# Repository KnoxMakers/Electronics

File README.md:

# Electronics
schematics, board files, firmware, slide decks, and the like

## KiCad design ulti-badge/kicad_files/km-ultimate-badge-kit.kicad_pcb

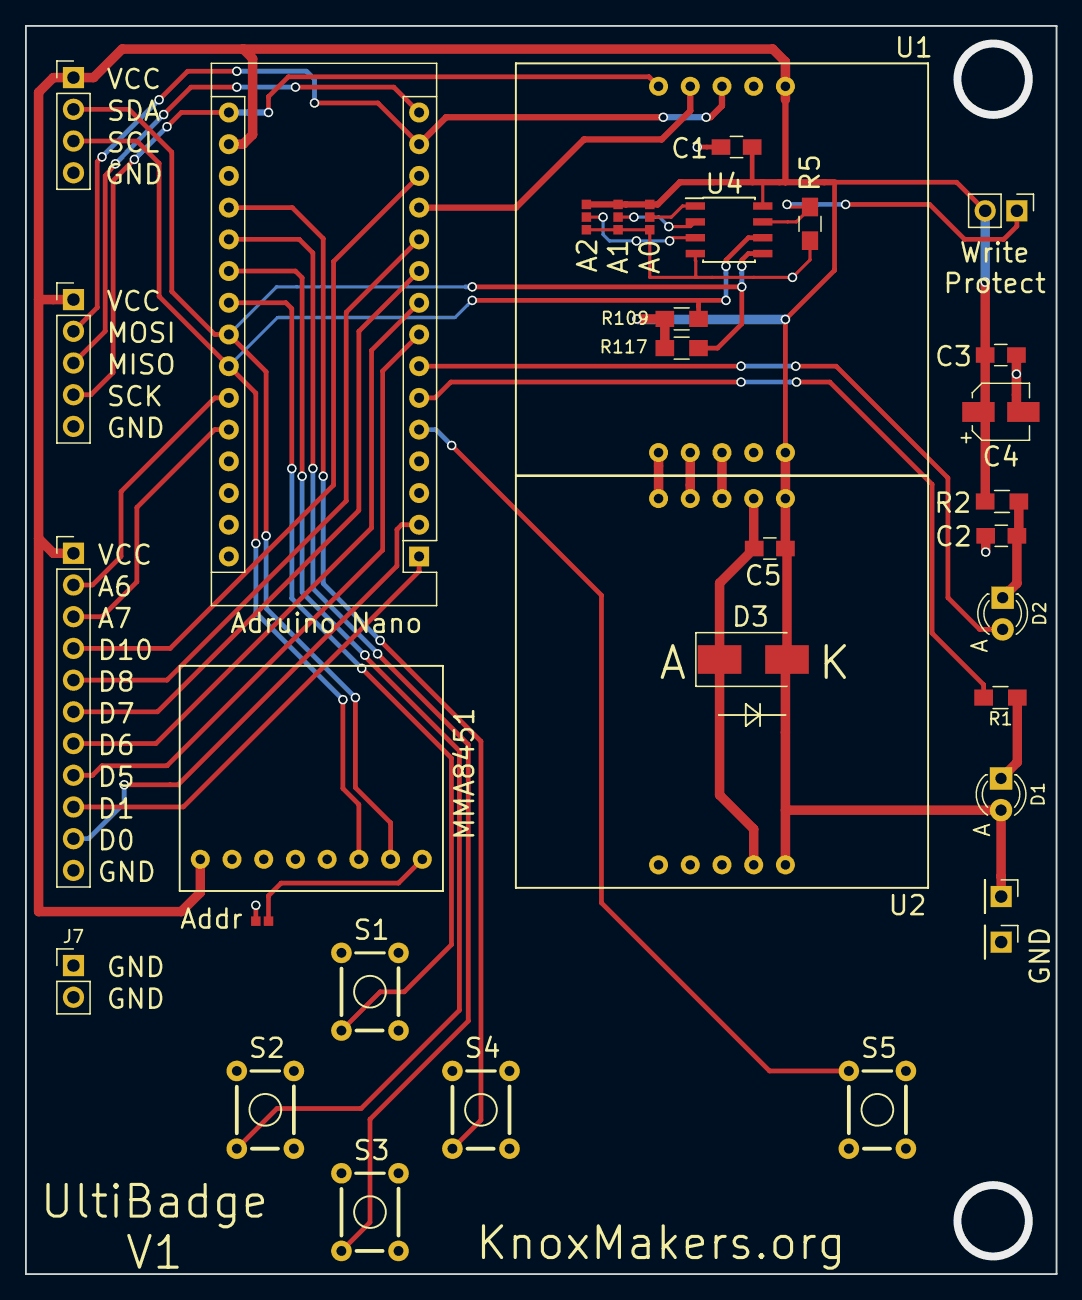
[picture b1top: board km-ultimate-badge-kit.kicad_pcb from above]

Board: 2 copper layers, 82.6 x 100.0 mm, 34 parts (0 on the bottom side), 34 nets.

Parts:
A1: Arduino_Nano_v3.x; Arduino_Nano
C1, C2, C5: 100n; C_0805_HandSoldering
C3: 0.1u; C_0805_HandSoldering
C4: 10u; CP_Elec_4x4.5
D1: LED; LED_D3.0mm
D2: D_Photo; LED_D3.0mm
D3: Diode; D_SMB_Handsoldering
J1: Conn_01x02_Male; Pin_Header_Straight_1x02_Pitch2.54mm
J2: Conn_01x11_Male; Pin_Header_Straight_1x11_Pitch2.54mm
J3, J4: Conn_01x01; Pin_Header_Straight_1x01_Pitch2.54mm
J5: Conn_01x04_Male; Pin_Header_Straight_1x04_Pitch2.54mm
J6: Conn_01x05_Male; Pin_Header_Straight_1x05_Pitch2.54mm
J7: Conn_01x02; Pin_Header_Straight_1x02_Pitch2.54mm
JP1, JP2, JP3: SolderJumper_3_Bridged12; SolderJumper_3_Pad
JP4: SolderJumper_2_Open; SolderJumper_2_Pad
R1: 20; R_0805_HandSoldering
R2: 100; R_0805_HandSoldering
R5: 10k; R_0805_HandSoldering
R109, R117: 4.7k; R_0805_HandSoldering
S1, S2, S3, S4, S5: Momentary_Push_Buttom_KM_6x6; Momentary_Push_Button_KM_6x6
U1, U2: 8x8_LED_Matrix; 8x8LED_Matrix
U3: MMA8451
U4: 24LC04; SOIC-8_3.9x4.9mm_Pitch1.27mm

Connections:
A6: A1.25, J2.2
A7: A1.26, J2.3
D0: A1.2, J2.10
D1: A1.1, J2.9
D5: A1.8, J2.8
D6: A1.9, J2.7
D7: A1.10, J2.6
D8: A1.11, J2.5
D10: A1.13, J2.4
DISPLAY_CS: A1.12, U1.4
GND: A1.4, A1.29, C1.2, C2.2, C3.2, C4.2, C5.2, D3.1, J2.11, J4.1, J5.4, J6.5, J7.1, J7.2, JP1.1, JP2.1, JP3.1, JP4.2, R5.1, S1.4, S2.4, S3.4, S4.4, S5.3, U1.2, U1.9, U2.2, U2.9, U3.2, U4.4
INT0: A1.5, S5.1
MISO: A1.15, J6.3
MOSI: A1.14, J6.2, U1.3
unnamed: C2.1, D2.1, R2.2
unnamed: D1.1, R1.1
unnamed: J1.1, R5.2, U4.7
unnamed: JP1.2, U4.3
unnamed: JP2.2, U4.2
unnamed: JP3.2, U4.1
unnamed: JP4.1, U3.8
unnamed: U1.6, U2.5
unnamed: U1.7, U2.4
unnamed: U1.8, U2.3
PB0: A1.19, S4.2
PB1: A1.20, S3.2
PB2: A1.21, S2.2
PB3: A1.22, S1.2
RX_DIODE: A1.7, D2.2
SCK: A1.16, J6.4, U1.5
SCL: A1.24, J5.3, R109.1, U3.6, U4.6
SDA: A1.23, J5.2, R117.1, U3.7, U4.5
TX_DIODE: A1.6, R1.2
VCC: A1.17, C1.1, C3.1, C4.1, C5.1, D1.2, D3.2, J1.2, J2.1, J3.1, J5.1, J6.1, JP1.3, JP2.3, JP3.3, R2.1, R109.2, R117.2, U1.1, U1.10, U2.1, U2.10, U3.1, U4.8

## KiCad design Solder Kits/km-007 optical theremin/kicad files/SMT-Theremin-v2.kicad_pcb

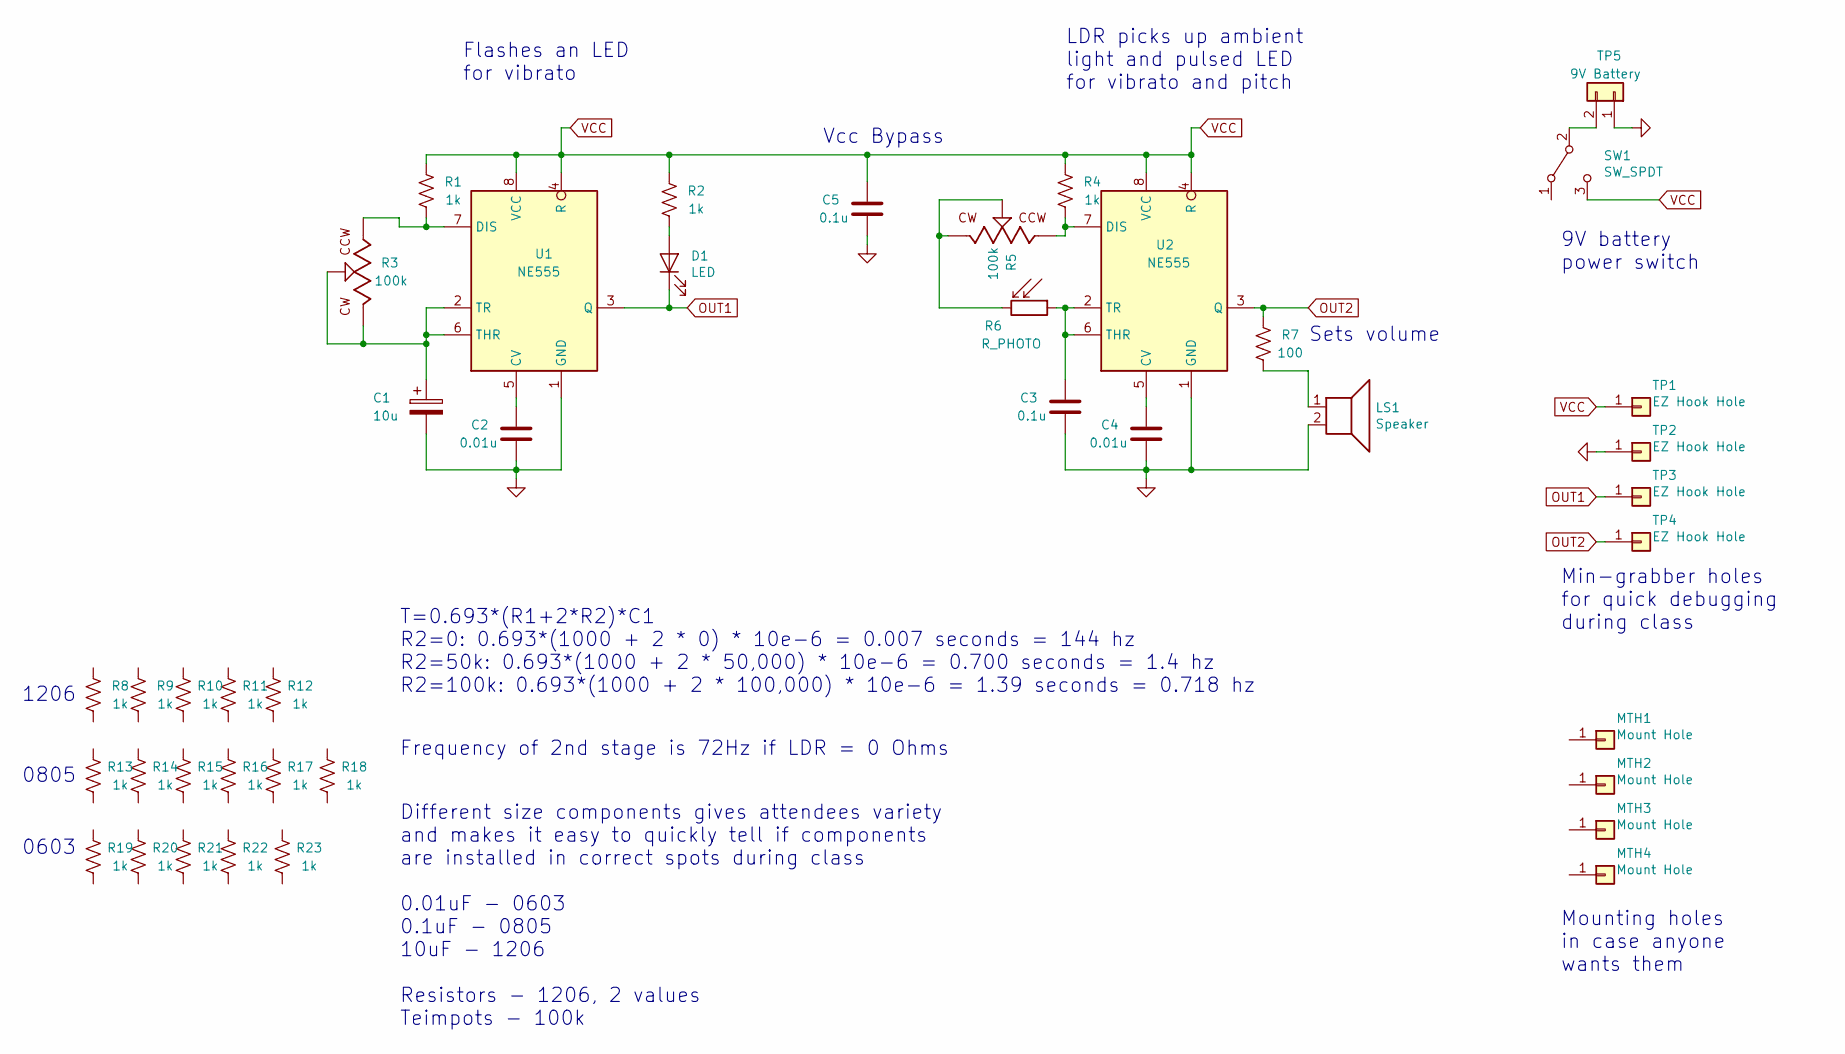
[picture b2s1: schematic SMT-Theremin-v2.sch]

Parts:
C1: 10u; C_1206_HandSoldering
C2, C4: 0.01u; C_0603_HandSoldering
C3, C5: 0.1u; C_0805_HandSoldering
D1: LED; D_0805_HandSoldering
LS1: Speaker; Speaker-40mm
MTH1, MTH2, MTH3, MTH4: Mount Hole; Mount-Hole-#4
R1, R2, R4, R8, R9, R10, R11, R12: 1k; R_1206_HandSoldering
R3, R5: 100k; Bourns-3386PT-xxx-xxxx
R6: R_PHOTO; R_LDR_5.1x4.3mm_P3.4mm_Vertical
R7: 100; R_1206_HandSoldering
R13, R14, R15, R16, R17, R18: 1k; R_0805_HandSoldering
R19, R20, R21, R22, R23: 1k; R_0603_HandSoldering
SW1: SW_SPDT; KM-SPDT-Slide
TP1, TP2, TP3, TP4: EZ Hook Hole; TP-Minigrabber-Edge-Via
TP5: 9V Battery; PinHeader_1x02_P2.54mm_Vertical
U1, U2: NE555; SOIC-8_3.9x4.9mm_P1.27mm

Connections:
GND: C1.2, C2.1, C3.1, C4.1, C5.1, LS1.2, TP2.1, TP5.1, U1.1 (GND), U2.1 (GND)
unnamed: C1.1, R3.2 (WIPER), R3.3 (CW), U1.2 (TR), U1.6 (THR)
unnamed: C2.2, U1.5 (CV)
unnamed: C3.2, R6.1, U2.2 (TR), U2.6 (THR)
unnamed: C4.2, U2.5 (CV)
unnamed: D1.2 (A), R2.1
unnamed: LS1.1, R7.1
unnamed: R1.1, R3.1 (CCW), U1.7 (DIS)
unnamed: R4.1, R5.1 (CCW), U2.7 (DIS)
unnamed: R5.2 (WIPER), R5.3 (CW), R6.2
unnamed: SW1.2 (B), TP5.2
OUT1: D1.1 (K), TP3.1, U1.3 (Q)
OUT2: R7.2, TP4.1, U2.3 (Q)
VCC: C5.2, R1.2, R2.2, R4.2, SW1.3 (C), TP1.1, U1.4 (R), U1.8 (VCC), U2.4 (R), U2.8 (VCC)

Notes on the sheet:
9V battery power switch
Min-grabber holes for quick debugging during class
Mounting holes in case anyone wants them
Flashes an LED for vibrato
LDR picks up ambient light and pulsed LED for vibrato and pitch
Different size components gives attendees variety and makes it easy to quickly tell if components are installed in correct spots during class 0.01uF - 0603 0.1uF - 0805 10uF - 1206 Resistors - 1206, 2 values Teimpots - 100k
Vcc Bypass
Sets volume
T=0.693*(R1+2*R2)*C1 R2=0: 0.693*(1000 + 2 * 0) * 10e-6 = 0.007 seconds = 144 hz R2=50k: 0.693*(1000 + 2 * 50,000) * 10e-6 = 0.700 seconds = 1.4 hz R2=100k: 0.693*(1000 + 2 * 100,000) * 10e-6 = 1.39 seconds = 0.718 hz
Frequency of 2nd stage is 72Hz if LDR = 0 Ohms
1206
0805
0603

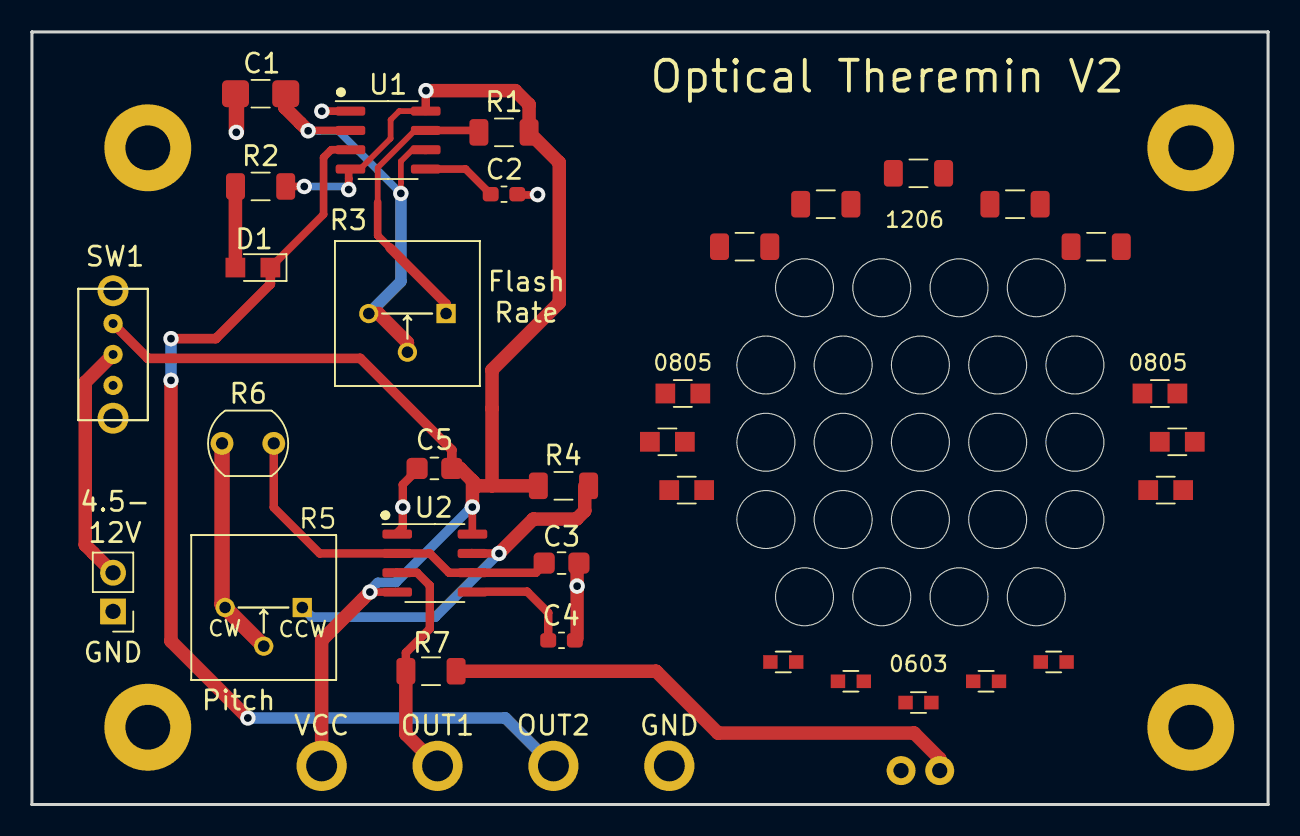
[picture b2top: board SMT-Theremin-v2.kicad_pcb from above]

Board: 2 copper layers, 81.3 x 50.8 mm, 42 parts (1 on the bottom side), 14 nets.

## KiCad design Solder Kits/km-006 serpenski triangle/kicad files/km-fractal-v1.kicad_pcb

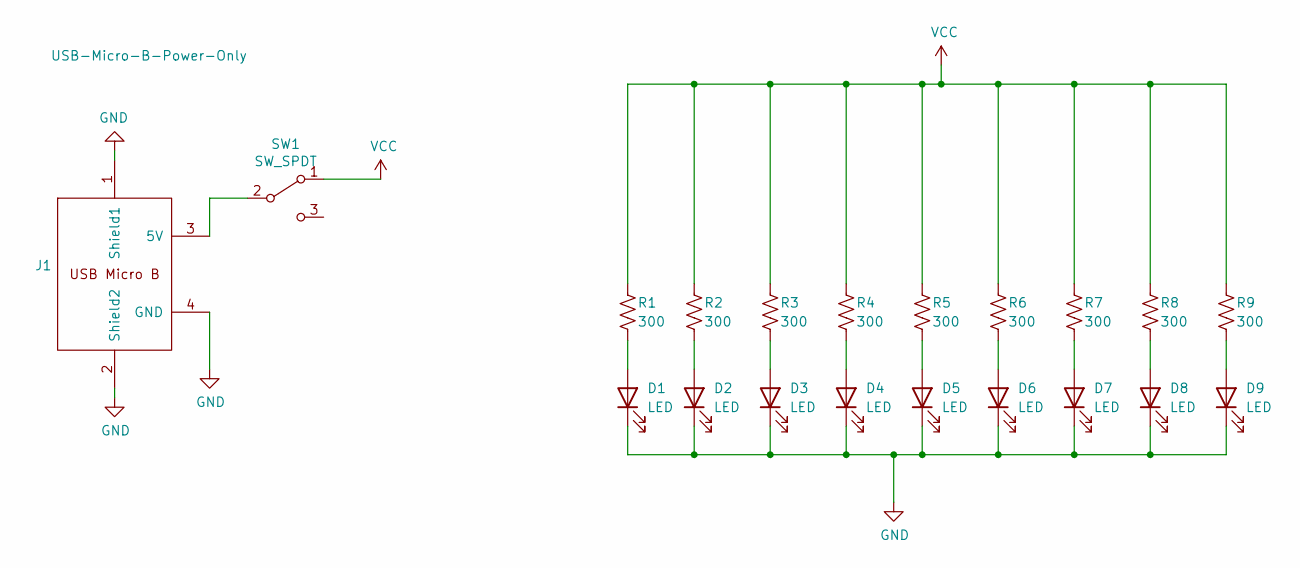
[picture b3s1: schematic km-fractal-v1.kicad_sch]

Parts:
D1, D2, D3, D4, D5, D6, D7, D8, D9: LED; LED_0805_2012Metric_Pad1.15x1.40mm_HandSolder
J1: USB-Micro-B-Power-Only; USB Micro-B Power Only
R1, R2, R3, R4, R5, R6, R7, R8, R9: 300; R_1206_HandSoldering
SW1: SW_SPDT; KM-SPDT-Slide

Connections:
GND: D1.1 (K), D2.1 (K), D3.1 (K), D4.1 (K), D5.1 (K), D6.1 (K), D7.1 (K), D8.1 (K), D9.1 (K), J1.1 (Shield1), J1.2 (Shield2), J1.4 (GND)
unnamed: D1.2 (A), R1.2
unnamed: D2.2 (A), R2.2
unnamed: D3.2 (A), R3.2
unnamed: D4.2 (A), R4.2
unnamed: D5.2 (A), R5.2
unnamed: D6.2 (A), R6.2
unnamed: D7.2 (A), R7.2
unnamed: D8.2 (A), R8.2
unnamed: D9.2 (A), R9.2
unnamed: J1.3 (5V), SW1.2 (B)
VCC: R1.1, R2.1, R3.1, R4.1, R5.1, R6.1, R7.1, R8.1, R9.1, SW1.1 (A)

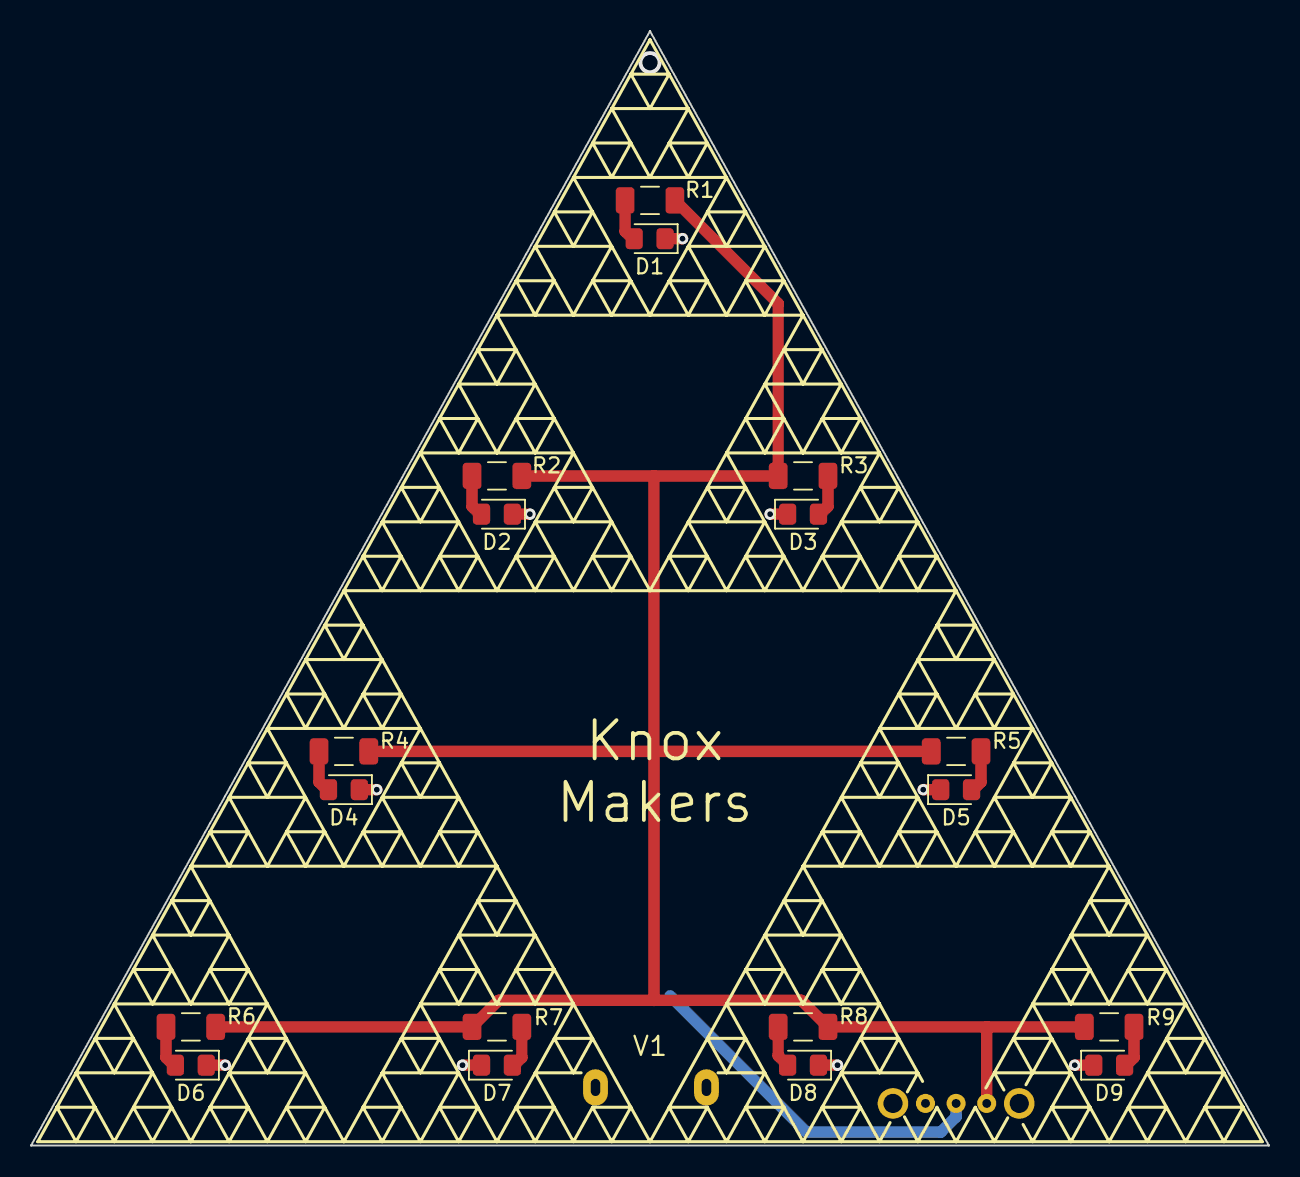
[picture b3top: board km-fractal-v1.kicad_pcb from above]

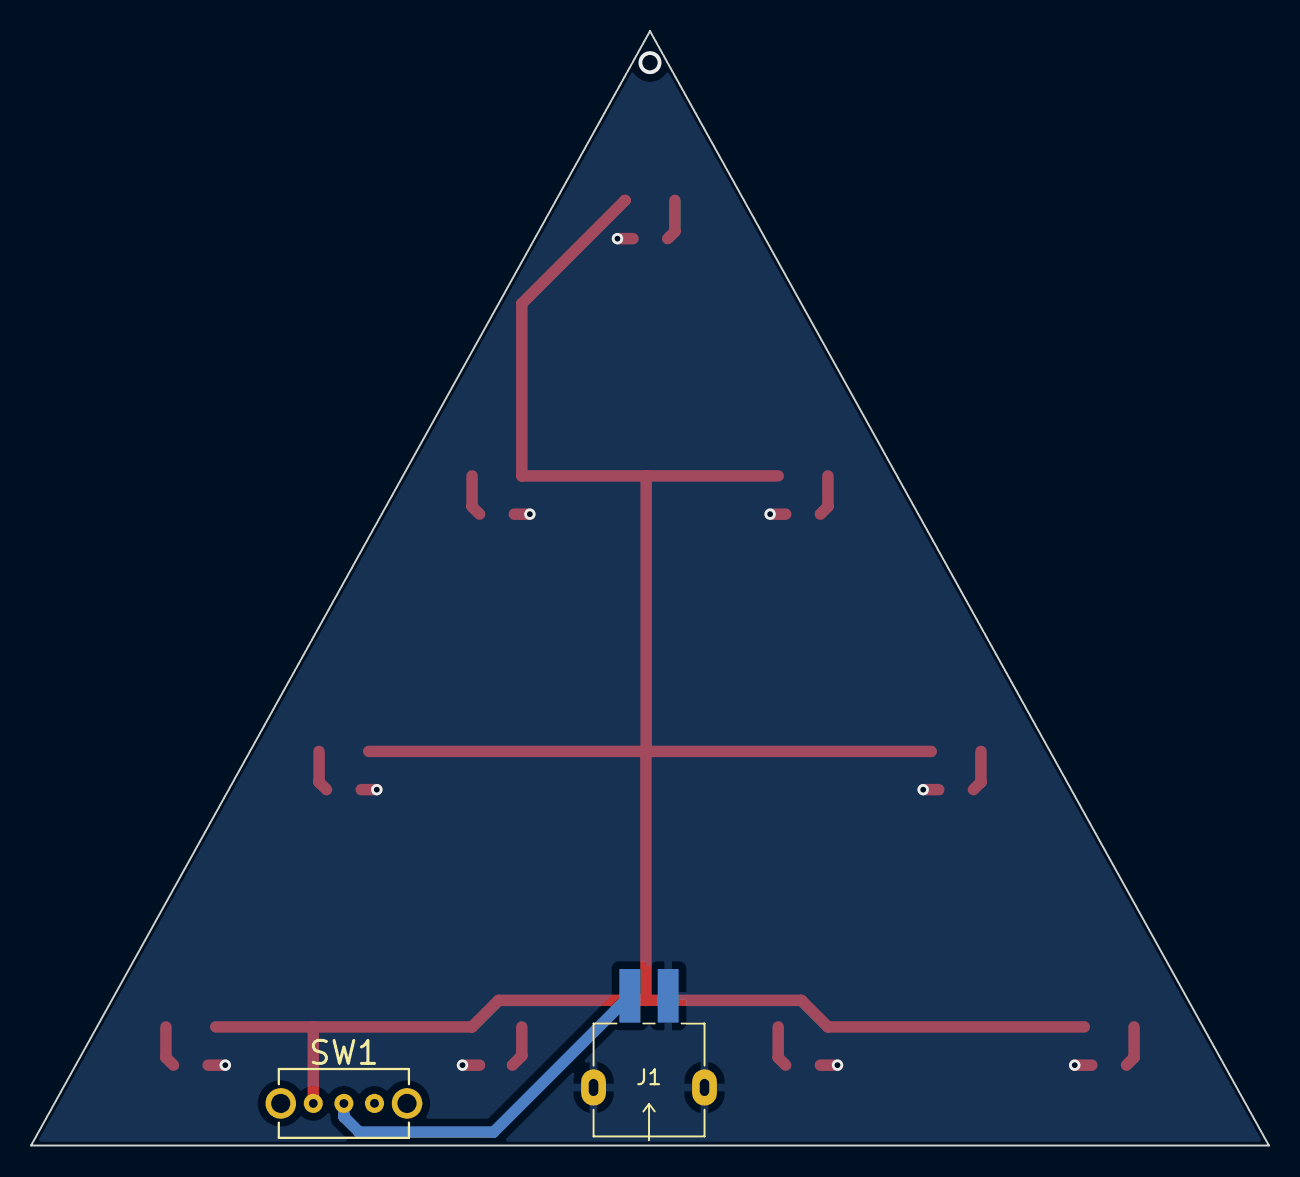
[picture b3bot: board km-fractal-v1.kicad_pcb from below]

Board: 2 copper layers, 82.2 x 74.0 mm, 20 parts (2 on the bottom side), 12 nets.

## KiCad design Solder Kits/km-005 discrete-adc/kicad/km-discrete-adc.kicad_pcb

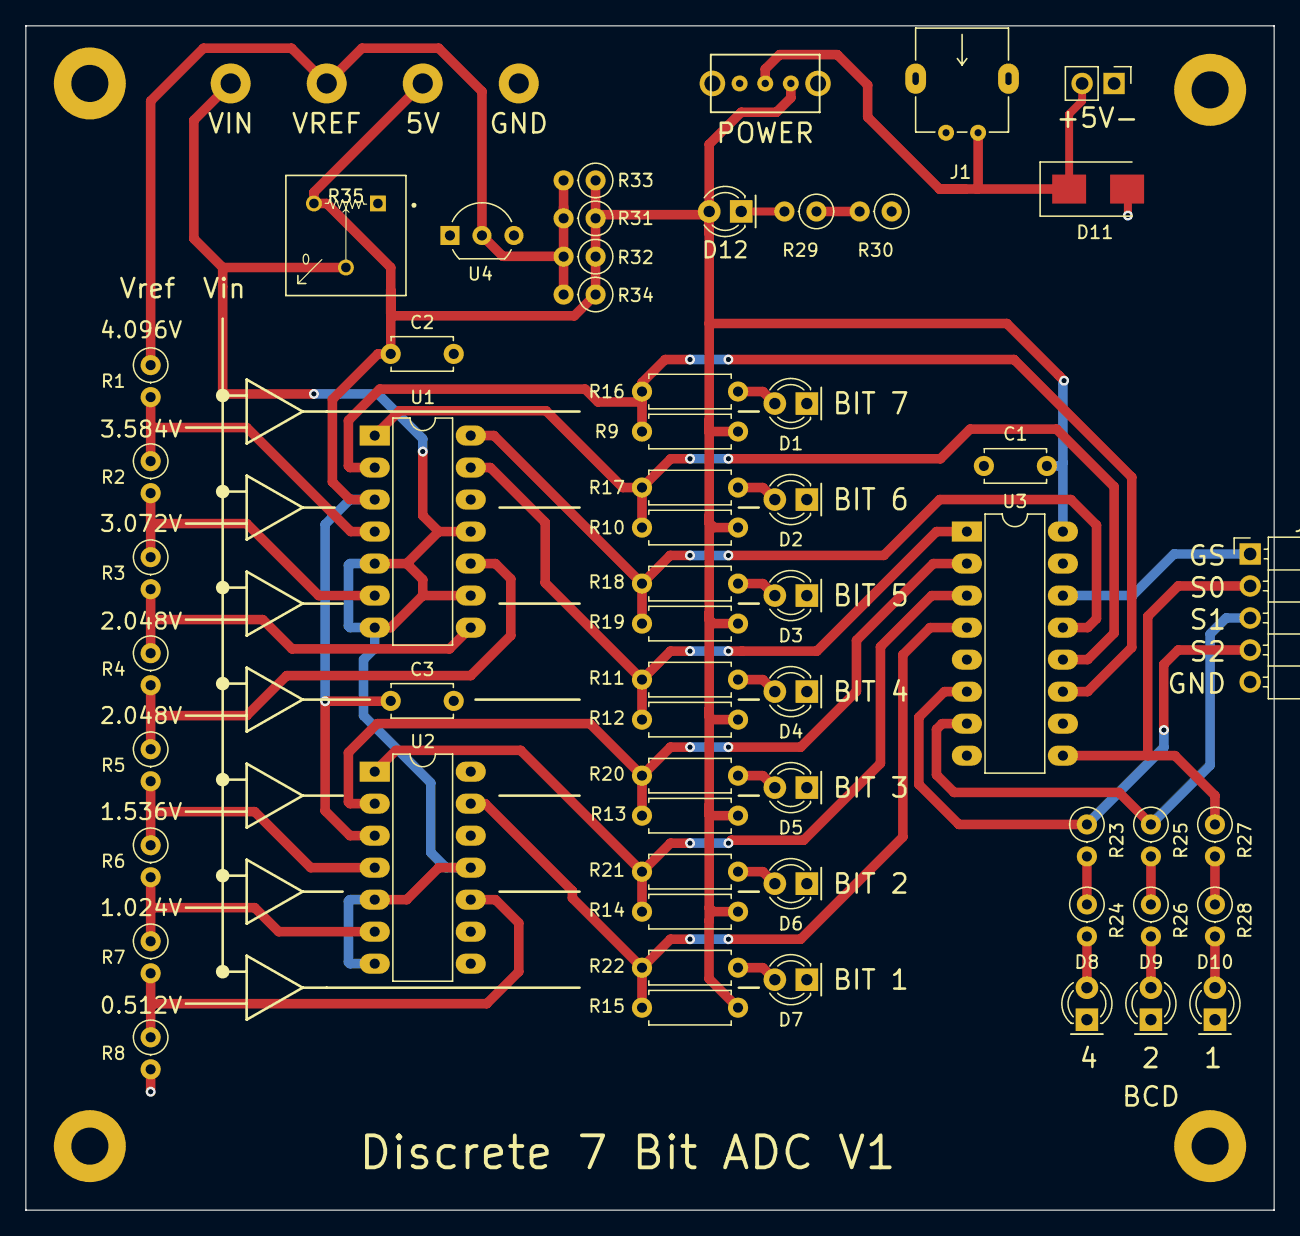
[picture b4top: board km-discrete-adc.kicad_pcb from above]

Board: 2 copper layers, 99.1 x 94.0 mm, 66 parts (0 on the bottom side), 38 nets.

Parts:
C1, C2, C3: 1u; C_Disc_D4.7mm_W2.5mm_P5.00mm
D1, D2, D3, D4, D5, D6, D7, D8, D9, D10, D12: LED; LED_D3.0mm
D11: D; D_SMB_Handsoldering
J1: USB-Micro-B-Power-Only; USB Micro-B Power Only
J4: OUTPUT; Pin_Header_Angled_1x05_Pitch2.54mm
MTH1, MTH2, MTH3, MTH4: Mount Hole; Mount-Hole-#4
MTH5, MTH6, MTH7, MTH8: Mount Hole; Keystone-5005
R1, R2, R3, R4, R5, R6, R7, R8, R23, R24, R25, R26, R27, R28, R29, R30, R31, R32, R33, R34: 4.7k; R_Axial_DIN0207_L6.3mm_D2.5mm_P2.54mm_Vertical
R9, R10, R11, R12, R13, R14, R15, R16, R17, R18, R19, R20, R21, R22: 4.7k; R_Axial_DIN0207_L6.3mm_D2.5mm_P7.62mm_Horizontal
R35: Bourns-3310Y-xxx-xxxx
SW1: SW_SPDT; KM-SPDT-Slide
TP1: VCC; Pin_Header_Straight_1x02_Pitch2.54mm
U1, U2: LM339; DIP-14_W7.62mm_LongPads
U3: 74LS148; DIP-16_W7.62mm_LongPads
U4: LM4030; TO-92_Inline_Wide

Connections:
+5V: C1.1, C2.1, C3.1, D12.2, MTH7.1, R9.1, R10.1, R11.1, R12.1, R13.1, R14.1, R15.1, R31.1, R32.1, R33.1, R34.1, R35.3, SW1.3, U1.3, U2.3, U3.16
/S0: J4.2, R27.1, U3.9
/S1: J4.3, R25.1, U3.7
/S2: J4.4, R23.1, U3.6
GND: C1.2, C2.2, C3.2, D1.1, D2.1, D3.1, D4.1, D5.1, D6.1, D7.1, D8.1, D9.1, D10.1, D11.2, J1.1, J1.2, J1.4, J4.5, MTH6.1, R8.2, R30.1, R35.1, TP1.1, U1.12, U2.12, U3.5, U3.8, U3.10, U4.3
GS: J4.1, U3.14
unnamed: D1.2, R16.2
unnamed: D2.2, R17.2
unnamed: D3.2, R18.2
unnamed: D4.2, R19.2
unnamed: D5.2, R20.2
unnamed: D6.2, R21.2
unnamed: D7.2, R22.2
unnamed: D8.2, R24.2
unnamed: D9.2, R26.2
unnamed: D10.2, R28.2
unnamed: D11.1, J1.3, SW1.2, TP1.2
unnamed: D12.1, R29.2
unnamed: R1.2, R2.1, U1.4
unnamed: R2.2, R3.1, U1.6
unnamed: R3.2, R4.1, U1.8
unnamed: R4.2, R5.1, U1.10
unnamed: R5.2, R6.1, U2.4
unnamed: R6.2, R7.1, U2.6
unnamed: R7.2, R8.1, U2.10
unnamed: R10.2, R17.1, U1.1, U3.12
unnamed: R11.2, R18.1, U1.14, U3.13
unnamed: R12.2, R19.1, U1.13, U3.1
unnamed: R13.2, R20.1, U2.2, U3.2
unnamed: R14.2, R21.1, U2.1, U3.3
unnamed: R15.2, R22.1, U2.13, U3.4
unnamed: R9.2, R16.1, U1.2, U3.11
unnamed: R23.2, R24.1
unnamed: R25.2, R26.1
unnamed: R27.2, R28.1
unnamed: R29.1, R30.2
VIN: MTH5.1, R35.2, U1.5, U1.7, U1.9, U1.11, U2.5, U2.7, U2.11
VREF: MTH8.1, R1.1, R31.2, R32.2, R33.2, R34.2, U4.2

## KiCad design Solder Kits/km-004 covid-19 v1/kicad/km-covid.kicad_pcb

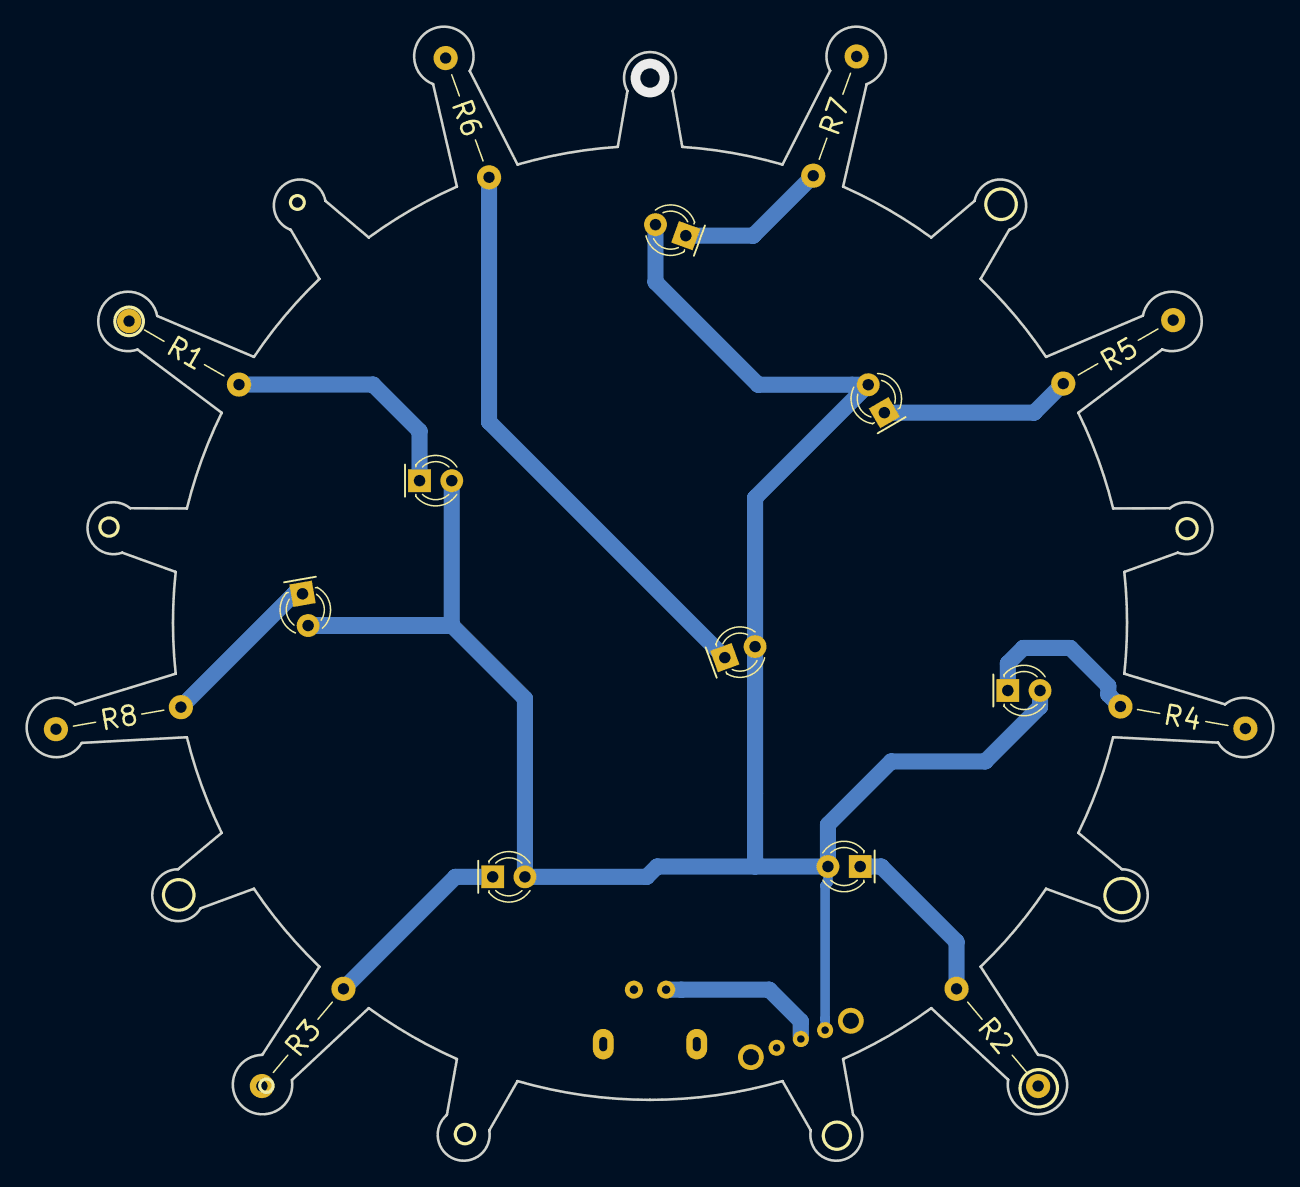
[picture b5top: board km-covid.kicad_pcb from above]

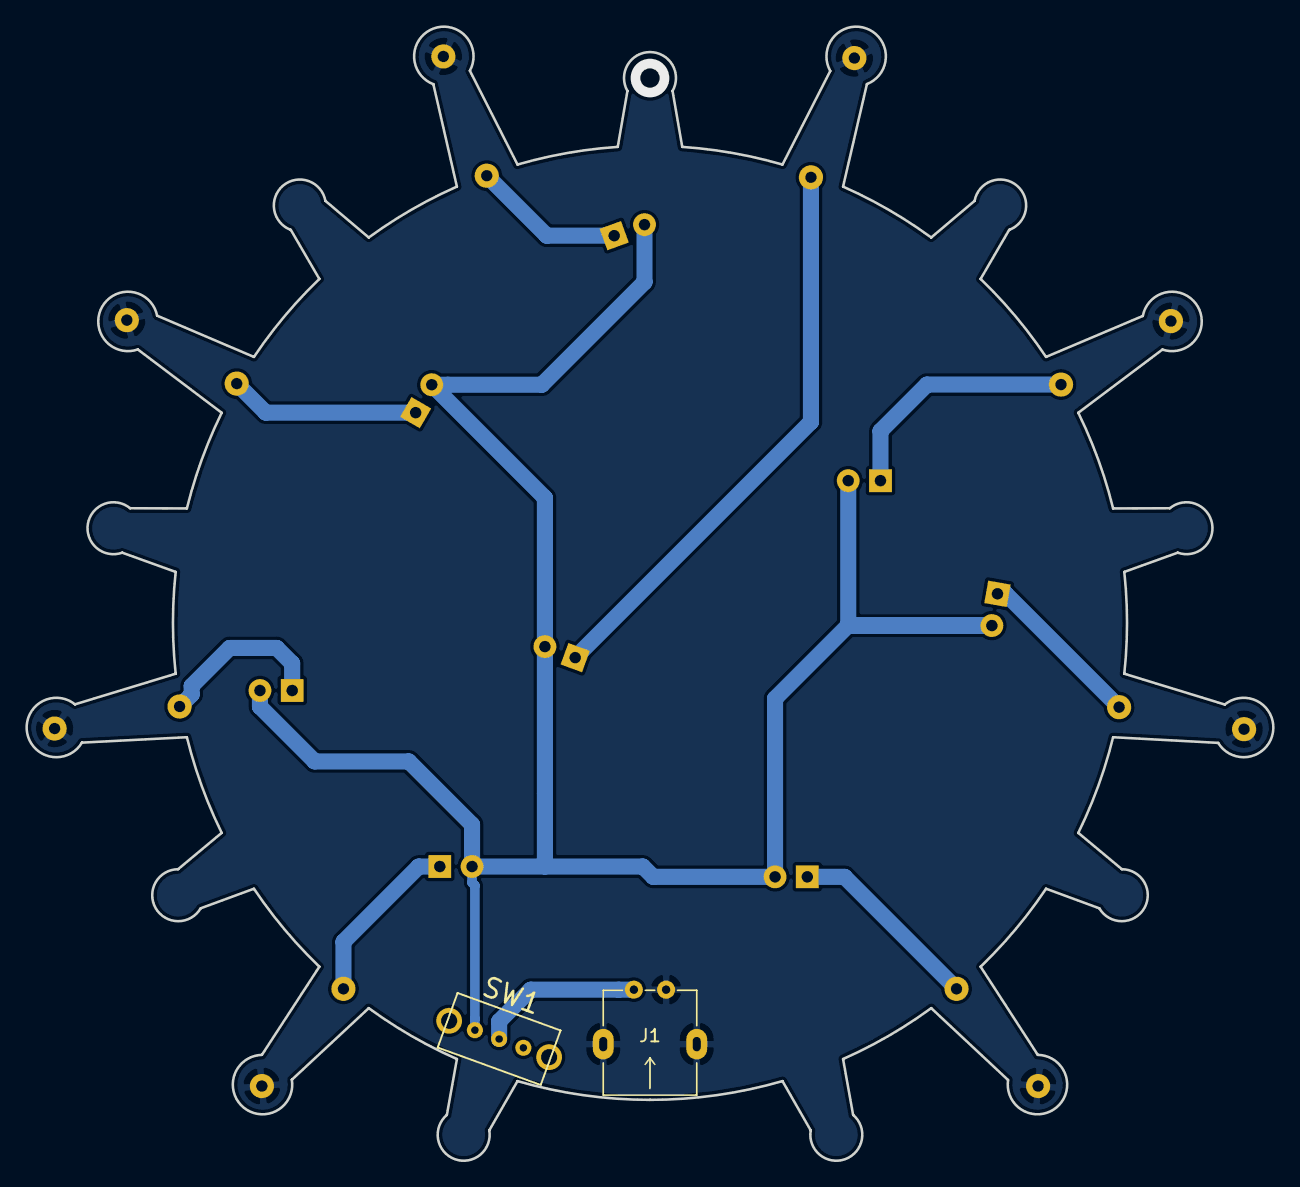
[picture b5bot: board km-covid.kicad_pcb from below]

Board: 2 copper layers, 98.2 x 89.4 mm, 18 parts (2 on the bottom side), 11 nets.

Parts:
D1, D2, D3, D4, D5, D6, D7, D8: LED; LED_D3.0mm
J1: USB-Micro-B-Power-Only; USB Micro-B Power Only
R1, R2, R3, R4, R5, R6, R7, R8: 300; R_Axial_Minimal_KM
SW1: SW_SPDT; KM-SPDT-Slide

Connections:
GND: J1.1, J1.2, J1.4, R1.1, R2.1, R3.1, R4.1, R5.1, R6.1, R7.1, R8.1
unnamed: D1.1, R1.2
unnamed: D2.1, R2.2
unnamed: D3.1, R3.2
unnamed: D4.1, R4.2
unnamed: D5.1, R5.2
unnamed: D6.1, R6.2
unnamed: D7.1, R7.2
unnamed: D8.1, R8.2
unnamed: J1.3, SW1.2
VCC: D1.2, D2.2, D3.2, D4.2, D5.2, D6.2, D7.2, D8.2, SW1.3

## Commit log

2019-02-08 Initial upload after class
2019-03-21 Created Classes directory and moved appropriate files there
2019-03-21 Created Ultibadge directory
    Some initial files
2019-03-21 mnor updates to badge files
2019-03-21 minor updates
2019-03-22 Added scrolling text, bouncing ball to ultibadge
2019-03-22 fixed a couple of link typos
2019-03-23 Added swtich test sketch to UltiBadge code examples
2019-03-23 Added switch test sketch to badge code examples
2019-03-23 Added eeprom-test sketch
2019-03-23 added i2c scanner sketch
2019-03-23 update github link
2019-03-23 updated links
2019-04-04 Added KM Badge Documentation
2019-04-09 updated abklit badge schematic and instructions
2019-04-09 add intro to solder kit folder
2019-04-09 fixed minor things in instructions
2019-09-11 intro to solder class v1 updates
2019-09-11 updates to solder kits
2019-09-11 solder kit updates
    a few file name changes
2019-12-05 Initial release holiday star kit v1
2019-12-05 Solder Kit Instructions Update
2019-12-05 adderd freq domain/filtering class material
2019-12-19 updated for filters class
2020-01-19 update for 1/19/2020 class
2022-09-18 organized around kit naming/numbers
2022-09-18 Fixed directory structure
2022-09-19 km-001 update
2022-09-20 file reorg
2022-09-20 file structure org
2022-09-25 km006 instructions
2023-01-04 Create KiCAD
2023-01-04 uploads
2023-01-20 Added Adv Serial Comms Class
2023-02-12 added feb 2023 transistors class
2023-02-12 added intro 101 class materials
2023-02-27 added macro keyboard class material
2023-03-02 macro keyboard v2
2023-03-03 macro keyboard v3
2023-03-03 macro keyboard v4
2023-03-13 added macro keyboard project revisions
2023-03-16 added macro keyboard v8
2023-07-16 adding classes
2023-09-09 update classes
2024-01-04 added ADC
2024-04-01 Added Intro Class
2024-04-01 removed files
2025-02-01 Macro Keyboard Class
2025-03-12 Add 2025-02-01 Macro Keypad Class
2025-12-04 Create 2025-12-06 RPi Pico Class
2025-12-04 Create Overview
2026-01-20 removed unused KiCAD
2026-01-20 changed case and removed spaces in some filenames
2026-03-07 Create 2026-03-07-Multitasking
